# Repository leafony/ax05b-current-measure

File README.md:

# Leafony AX05B

Leafony AX05B I Measは、Leafonyバスの`V33`と`VBUS`の電流測定用リーフです。
Nordic Power Profiler Kit II（PPK2）などの外部電流測定器を電源ラインに直列に入れられるよう、`V33`と`VBUS`をそれぞれ`IN`/`OUT`に分離しています。

| Top | Bottom |
| --- | --- |
|  |  |

## 仕様

| 項目 | 内容 |
| --- | --- |
| リーフ名 | Leafony AX05B I Meas |
| 用途 | Leafonyバスの電源ライン電流測定 |
| 測定対象 | `V33`、`VBUS` |
| バスコネクタ | Leafony Bus（F29/B29） |
| 測定コネクタ | 1x4、2.54mmピッチ、ライトアングルピンヘッダ x 2 |
| 基板外形 | 20mm x 20mm |
| 基板厚 | 0.8mm |
| 層構成 | 2層 |
| 表面処理 | ENIG（Immersion gold） |
| 回路図 | [docs/leafony-ax05b-sch.pdf](docs/leafony-ax05b-sch.pdf) |
| レイアウト | [docs/leafony-ax05b-layout.pdf](docs/leafony-ax05b-layout.pdf) |

## 測定コネクタ

`J1`が`V33`、`J2`が`VBUS`です。どちらもピン配置は同じです。

| ピン | J1（V33） | J2（VBUS） | 用途 |
| --- | --- | --- | --- |
| 1 | `GND` | `GND` | 測定器のGND |
| 2 | `V33OUT` | `VBUSOUT` | 測定後の出力側 |
| 3 | `V33IN` | `VBUSIN` | 測定前の入力側 |
| 4 | `GND` | `GND` | 測定器のGND |

## Nordic Power Profiler Kit IIでの電流測定

PPK2を電流計として使用し、測定したい電源ラインの`IN`と`OUT`の間に直列接続します。

- `V33`を測定する場合: `J1`の`V33IN`と`V33OUT`の間にPPK2を接続します。
- `VBUS`を測定する場合: `J2`の`VBUSIN`と`VBUSOUT`の間にPPK2を接続します。
- GND基準が必要な場合は、同じコネクタの`GND`ピンをPPK2のGNDへ接続します。

測定しない電源ラインは、`IN`と`OUT`をジャンパーでショートしてください。
例えば`V33`を測定しない場合は`J1`の2-3ピンを、`VBUS`を測定しない場合は`J2`の2-3ピンをショートします。
両方を測定しない通常使用時は、`J1`と`J2`の両方で2-3ピンをショートしてください。

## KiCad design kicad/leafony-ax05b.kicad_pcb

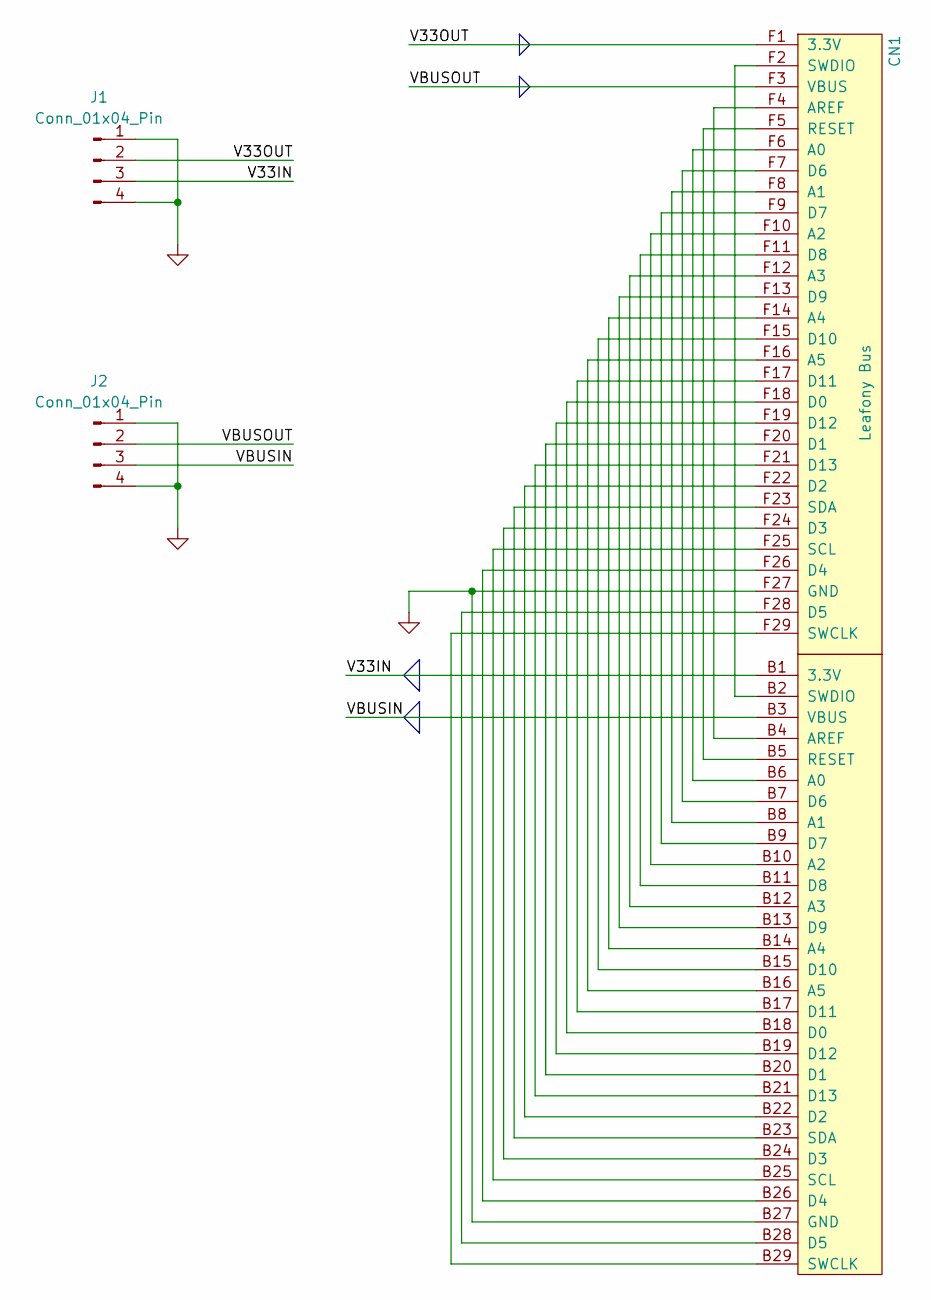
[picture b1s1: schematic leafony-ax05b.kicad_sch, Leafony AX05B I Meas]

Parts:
CN1: Leafony Bus; CN_F29_B29
J1, J2: Conn_01x04_Pin; PinHeader_1x04_P2.54mm_Horizontal

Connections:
/V33IN: CN1.B1 (3.3V), J1.3
/V33OUT: CN1.F1 (3.3V), J1.2
/VBUSIN: CN1.B3 (VBUS), J2.3
/VBUSOUT: CN1.F3 (VBUS), J2.2
GND: CN1.B27 (GND), CN1.F27 (GND), J1.1, J1.4, J2.1, J2.4
unnamed: CN1.B6 (A0), CN1.F6 (A0)
unnamed: CN1.B8 (A1), CN1.F8 (A1)
unnamed: CN1.B10 (A2), CN1.F10 (A2)
unnamed: CN1.B12 (A3), CN1.F12 (A3)
unnamed: CN1.B14 (A4), CN1.F14 (A4)
unnamed: CN1.B16 (A5), CN1.F16 (A5)
unnamed: CN1.B4 (AREF), CN1.F4 (AREF)
unnamed: CN1.B18 (D0), CN1.F18 (D0)
unnamed: CN1.B20 (D1), CN1.F20 (D1)
unnamed: CN1.B22 (D2), CN1.F22 (D2)
unnamed: CN1.B24 (D3), CN1.F24 (D3)
unnamed: CN1.B26 (D4), CN1.F26 (D4)
unnamed: CN1.B28 (D5), CN1.F28 (D5)
unnamed: CN1.B7 (D6), CN1.F7 (D6)
unnamed: CN1.B9 (D7), CN1.F9 (D7)
unnamed: CN1.B11 (D8), CN1.F11 (D8)
unnamed: CN1.B13 (D9), CN1.F13 (D9)
unnamed: CN1.B15 (D10), CN1.F15 (D10)
unnamed: CN1.B17 (D11), CN1.F17 (D11)
unnamed: CN1.B19 (D12), CN1.F19 (D12)
unnamed: CN1.B21 (D13), CN1.F21 (D13)
unnamed: CN1.B5 (RESET), CN1.F5 (RESET)
unnamed: CN1.B25 (SCL), CN1.F25 (SCL)
unnamed: CN1.B23 (SDA), CN1.F23 (SDA)
unnamed: CN1.B29 (SWCLK), CN1.F29 (SWCLK)
unnamed: CN1.B2 (SWDIO), CN1.F2 (SWDIO)

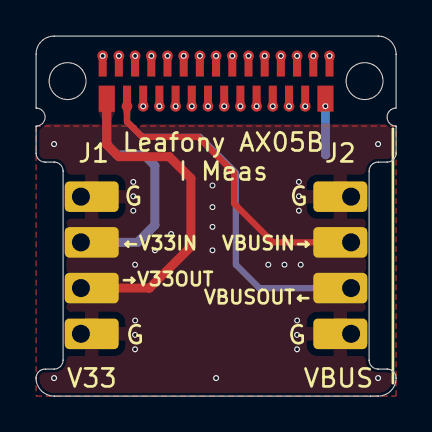
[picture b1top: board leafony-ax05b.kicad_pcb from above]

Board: 2 copper layers, 20.0 x 20.0 mm, 3 parts (0 on the bottom side), 31 nets.

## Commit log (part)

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2026-06-04 README.mdを更新し、Leafony AX05B I Measの仕様と接続方法を追加。関連する画像とPDFドキュメントを新規追加。回路図とレイアウトのPDFも追加。PCBファイル内のネット名を修正。
